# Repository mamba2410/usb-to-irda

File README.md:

# USB to IrDA converter board

# THIS IS UNTESTED, DO NOT BUILD YET

## What is this?

This is a USB to IrDA adapter. Plug it into a computer and it will appear as a
serial/COM port.
Anything you write to that port will come out over the IR transceiver at the
top, encoded using the IrDA standard.

This was made to interface with the Pokewalker, since other IrDA adapter boards
are either expensive or not very sleek.

You can also plug in a UART cable if you want.
It uses the [Raspberry Pi UART/Debug spec](https://datasheets.raspberrypi.com/debug/debug-connector-specification.pdf).
Cables to adapt to 0.1" headers should be easily purchaseable online.
Pinouts are labeled on the board for UART TX and RX, and SWD data and clock.
There is also a pin header hole for the NRST pin to connect to an ST-link.

The product name is "USB to IrDA" and the vendor name is "mamba2410".

## Instructions

Until I/someone makes a JLC PCBA project for this, you will need to buy the 
parts yourself and assemble by hand.
All you should need is a soldering iron and needle-nose tweezers.
Hot air might help, if you have it available.
The parts have been chosen specifically so that you don't need special tools.

Tips:

- Change your soldering iron tip depending on the part.
    - A knife tip for the MCU, USB connector and IR transceiver might help.
    - Small chisel tip for the capacitors, LEDs and resistors.
- Use lots of flux.
- The direction of LEDs matter. Unfortunately there's no easy way to tell which
  is the right way.
  You can check the datasheet and use a microscope to tell, or just try one way
  and if it doesn't light up, try the other.
- Try not to spend too much time on a single part, only a few seconds at a
  time. Spending longer might risk damaging the component, especially the LEDs.
- Consider buying spares, especially for the passives (resistors, capacitors,
  LEDs) since they can be lost or damaged easily.

### Board

Order from your favourite PCB fab. Files provided will be for JLC. If you want
others (e.g. PCBway) then you'll have to generate them yourself from the KiCad
files.

This is a 2-layer board, 1.6mm thickness, lead-free HASL finish.
Don't bother with the stencil unless you want to use a hot plate/reflow oven/
hot air and solder paste.
You should be able to buy 5 bare PCBs for around $3 plus shipping.

### Parts

- IrDA transceiver x 1- TFBS4711 (either TR1 or TT1)
- MCU x 1- STM32C071FBP6 (NOT the -N varaint)
- USB connector x 1 of either:
  - 12402012E212A (Amphenol)
  - USB4215-03-A (GCT)
- 3.3V regulator x 1 - TLV1117LV33DCYR
- UART connectors x 1 - SM03B-SRSS-TB (or x2 if you want the debug header)
- Buttons x 2 - B3FS1012P
- 5.1k resistors x 12 - RC0603FR-105K1L
- 47R resistor x 2 - RC0603FR-1047RL
- 0.1u capacitor x 2 - MCASE168SB5104KTNA01
- 1u capacitor x 2 - LMK107BJ105MAHT
- 4.7u capacitors x 2 - LMK107BJ475KA-T
- LEDs x 4 
  - Green/yellow (574 nm) - KG EELP41.22-PHRH-35-A8J8-20-R18 
  - Yellow (590 nm) - 150060YS83000
  - Red (624 nm) - KR EELP41.22-Q1S1-36-A8J8-020-R18
  - Amber (610 nm) - 150060AS83000 
  - Blue (465 nm) - 150060BS83000 
  - Green (527 nm) - KT EELP41.12-S2U1-25-2X4X-5-R18 
  - White - KW EELP41.RU-S1U1-3K6L-3X4X-5-R18

Checked on Mouser USA and it cost $12 plus shipping and taxes for enough to
make one.
Building in quantity (10+) will significantly drop this price per unit.

There are four LEDs, TX activity, RX activity, power status and a spare.
Pick and choose which colour you want.
Use [this website](https://405nm.com/wavelength-to-color/) to get an idea of
the colour of each by putting in the wavelength (e.g. 590 nm).
Different colours will need different resistor values. There are two pads for
resistors in parallel so that you can have 2 x 5.1k resistors in parallel for 
approx 2.5k total resistance.
If going for different values, you do not need to populate both.

### Enclosure

Enclosure is made using FreeCad 1.0.
An STL file will be provided to be able to 3d print.
You can either print this yourself, or get a bureau service to do it, like JLC.

You will need 4x M3 x 12mm screws and 4x M3 nuts.

### Programming

You will need to download [STM32CubeProgrammer](https://www.st.com/en/development-tools/stm32cubeprog.html),
unfortunately.

1. Plug the device in to your PC. Hold the `Boot` button then press the "Reset"
  button. This will cause the device to enter the DFU bootloader mode.
  The "user" LED should be lit up.
2. There are firmware files in the "releases" tab on the right in GitHub.
  Download either the `.elf` or `.dfu` file.
3. Open STM32CubeProgrammer.
  On the right there should be a dropdown box and a "connect" button.
  Change the dropdown from "ST-LINK" to "USB".
  In the "port" section below, select the device. There will probably only be one.
  If you do not see it there, click refresh to the right.
  If it is still not there, ensure the device is in bootloader mode.
  Click "connect".
4. In the tab on the left, click the "+" tab and choose "open file".
  Select the `.elf` file you downloaded in step 2.
5. Click "Download" near the top right.
  If all goes well, there should be a success popup.
6. Click "disconnect", then unplug your device and plug it back in.

Your device should now be flashed with the latest firmware, and show up as a
USB COM port.

## Development

If you want to play with the KiCad files, you can. There is a project library 
called `irda` which contains custom symbols, footprints and models of the
components used.

Generating the KiKit files from the KiCad shell

```bash
kikit panelize -p kikit.json .\irda-stm32.kicad_pcb panelized\panelized.kicad_pcb
```

To edit the firmware, you'll need
[STM32CubeIDE](https://www.st.com/en/development-tools/stm32cubeide.html).

If you want to debug, you'll need to solder the SWD header. Its the same as
the UART header.
You can also add a 0.1" header for the NRST pin to connect to an ST-link.

If you want to edit the 3D files, use FreeCad 1.0 or higher.

## License

Free to use/modify/sell. Do whatever you want with this. Just don't blame me if
it doesn't work or breaks something else.

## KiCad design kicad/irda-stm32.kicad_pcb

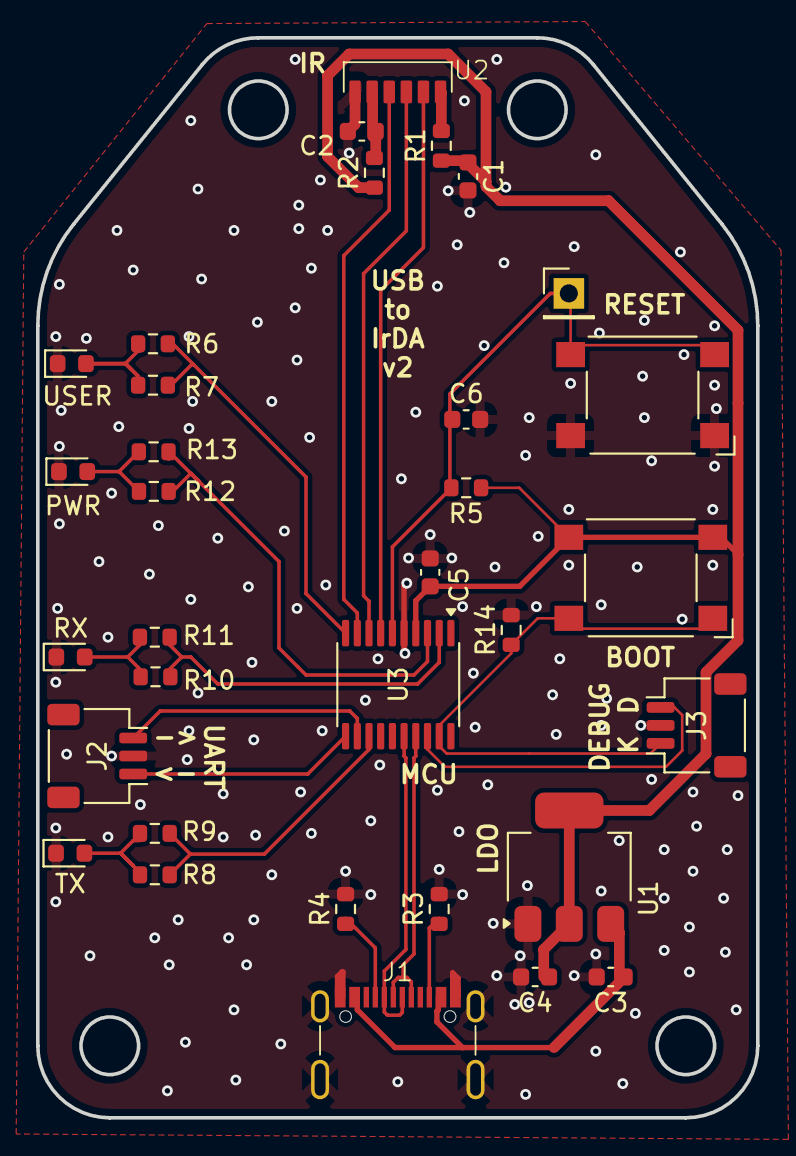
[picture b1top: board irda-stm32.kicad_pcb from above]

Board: 2 copper layers, 40.0 x 60.0 mm, 33 parts (0 on the bottom side), 25 nets.

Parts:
C1, C5: 4.7u; C_0603_1608Metric
C2, C6: 0.1u; C_0603_1608Metric
C3, C4: 1u; C_0603_1608Metric
D1: USER; LED_0603_1608Metric
D2: TX; LED_0603_1608Metric
D3: RX; LED_0603_1608Metric
D4: PWR; LED_0603_1608Metric
J1: USB_C_Receptacle_USB2.0_16P; GCT_USB4215_03_A
J2: UART; JST_SH_SM03B-SRSS-TB_1x03-1MP_P1.00mm_Horizontal
J3: SWD; JST_SH_SM03B-SRSS-TB_1x03-1MP_P1.00mm_Horizontal
R1, R2: 47R; R_0603_1608Metric
R3, R4, R5, R6, R7, R8, R9, R10, R11, R12, R13, R14: 5k1; R_0603_1608Metric
SW1: NRST_BUT; SW_SPST_Omron_B3FS-100xP
SW2: BOOT0_BUT; SW_SPST_Omron_B3FS-100xP
TP1: NRST; PinHeader_1x01_P2.54mm_Vertical
U1: TLV1117LV33DCYR; SOT-223-3_TabPin2
U2: TFBS4711; TFBS4711-TR
U3: STM32C071FBPx; TSSOP-20_4.4x6.5mm_P0.65mm

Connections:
+3.3V: C1.1, C4.1, C5.1, R1.1, R2.1, R5.1, SW2.2, U1.2 (OUT), U3.4 (VDD)
/CC1: J1.A5 (CC1), R4.1
/CC2: J1.B5 (CC2), R3.1
/EXT_RX: J2.1, U3.12 (PA5)
/EXT_TX: J2.3, U3.11 (PA4)
/IRDA_RX: U2.3 (RXD), U3.8 (PA1)
/IRDA_SD: U2.4 (SD), U3.9 (PA2)
/IRDA_TX: U2.2 (TXD), U3.7 (PA0)
/NRST: C6.1, R5.2, SW1.2, TP1.1, U3.6 (PF2)
/POWER_LED: R12.1, R13.1, U3.3 (PC15)
/RX_LED: R10.1, R11.1, U3.2 (PC14)
/SWCLK: J3.1, R14.1, SW2.1, U3.19 (PA14/PA15)
/SWDIO: J3.3, U3.18 (PA13)
/TX_LED: R8.1, R9.1, U3.13 (PA6)
/USB_DN: J1.A7 (D-), J1.B7 (D-), U3.16 (PA11)
/USB_DP: J1.A6 (D+), J1.B6 (D+), U3.17 (PA12)
/USER_LED: R6.1, R7.1, U3.10 (PA3)
/VUSB: C3.1, J1.A4 (VBUS), J1.A9 (VBUS), J1.B4 (VBUS), J1.B9 (VBUS), U1.3 (IN)
GND: C1.2, C2.2, C3.2, C4.2, C5.2, C6.2, D1.1 (K), D2.1 (K), D3.1 (K), D4.1 (K), J1.A1 (GND), J1.A12 (GND), J1.B1 (GND), J1.B12 (GND), J1.S1 (SHIELD), J2.2, J3.2, R3.2, R4.2, R14.2, SW1.1, U1.1 (GND), U2.6 (GND), U3.5 (VSS)
unnamed: D1.2 (A), R6.2, R7.2
unnamed: D2.2 (A), R8.2, R9.2
unnamed: D3.2 (A), R10.2, R11.2
unnamed: D4.2 (A), R12.2, R13.2
unnamed: C2.1, R2.2, U2.5 (VCC1)
unnamed: R1.2, U2.1 (VCC2)

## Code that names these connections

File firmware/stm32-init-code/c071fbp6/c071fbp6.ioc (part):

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Mcu.Name=STM32C071FBPx
Mcu.Package=TSSOP20_GP
Mcu.UserName=STM32C071FBPx
PA0.GPIOParameters=GPIO_Label
PA0.GPIO_Label=IRDA_TX
PA0.Mode=IrDA
PA0.Signal=USART1_TX
PA1.GPIOParameters=GPIO_Label
PA1.GPIO_Label=IRDA_RX
PA1.Mode=IrDA
PA1.Signal=USART1_RX
PA11\ [PA9].Mode=Device
PA11\ [PA9].Signal=USB_DM
PA12\ [PA10].Mode=Device
PA12\ [PA10].Signal=USB_DP
PA13.Mode=Serial_Wire
PA13.Signal=DEBUG_SWDIO
PA14-BOOT0.Mode=Serial_Wire
PA14-BOOT0.Signal=DEBUG_SWCLK
PA14-BOOT0__PA15.StandardMode=true
PA2.GPIOParameters=GPIO_Label
PA2.GPIO_Label=IRDA_SD
PA2.Signal=GPIO_Output
PA3.GPIOParameters=GPIO_Label
PA3.GPIO_Label=USER_LED
PA3.Signal=GPIO_Output
PA4.Mode=Asynchronous
PA4.Signal=USART2_TX
PA5.Mode=Asynchronous
PA5.Signal=USART2_RX
PA6.GPIOParameters=GPIO_Label
PA6.GPIO_Label=TX_LED
PA6.Signal=GPIO_Output
PB3__PB4__PB5__PB6.StandardMode=true
PB7__PB8.StandardMode=true
PC14-OSCX_IN(PC14).GPIOParameters=GPIO_Label
PC14-OSCX_IN(PC14).GPIO_Label=RX_LED
PC14-OSCX_IN(PC14).Signal=GPIO_Output
PC15-OSCX_OUT(PC15).GPIOParameters=GPIO_Label
PC15-OSCX_OUT(PC15).GPIO_Label=POWER_LED
PC15-OSCX_OUT(PC15).Signal=GPIO_Output
PF2-NRST.GPIOParameters=GPIO_Label
PF2-NRST.GPIO_Label=NRST
PF2-NRST.Signal=GPIO_Input
RCC.HSE_VALUE=8000000
RCC.SYSCLKFreq_VALUE=48000000
board=custom

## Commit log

2025-10-04 add enclsoure
2025-10-05 add c071fbp6 init helper
2025-10-05 update kicad, idk
2025-10-05 docs update
2025-10-05 update PCB for c071fbp6
2025-10-05 widen resistor spacing
2025-11-23 fix BOOT0 button and USB ground
2025-11-23 add blank stm32cube project
2025-11-23 add firmware source files
2025-11-23 update readmes
2025-11-23 explicitly set RDP level to stop device from bricking itself
2026-02-08 add lcsc/jlc part numbers and fix ir filters
2026-02-08 update gitignore
